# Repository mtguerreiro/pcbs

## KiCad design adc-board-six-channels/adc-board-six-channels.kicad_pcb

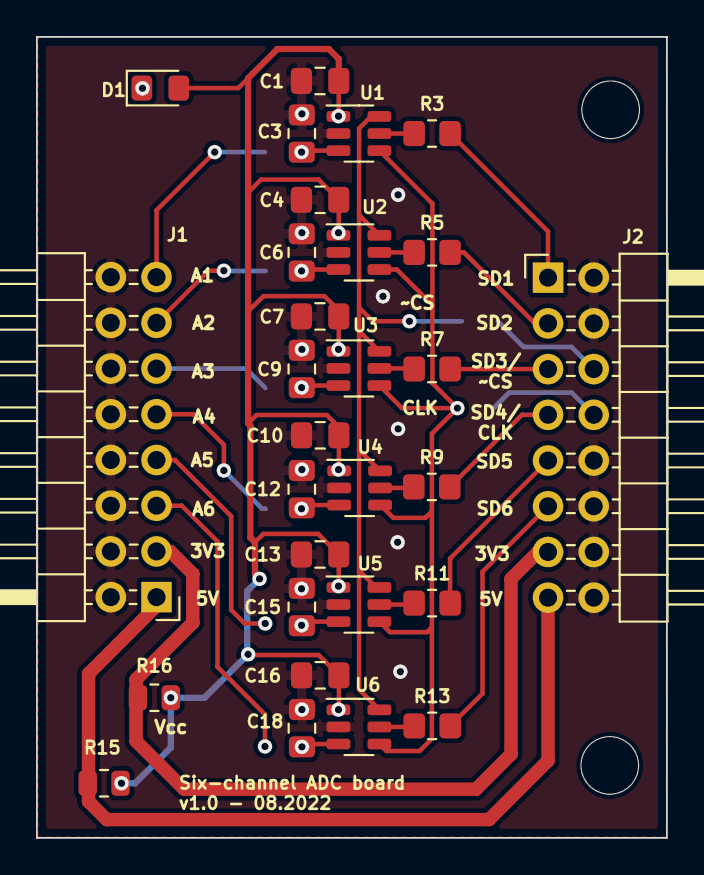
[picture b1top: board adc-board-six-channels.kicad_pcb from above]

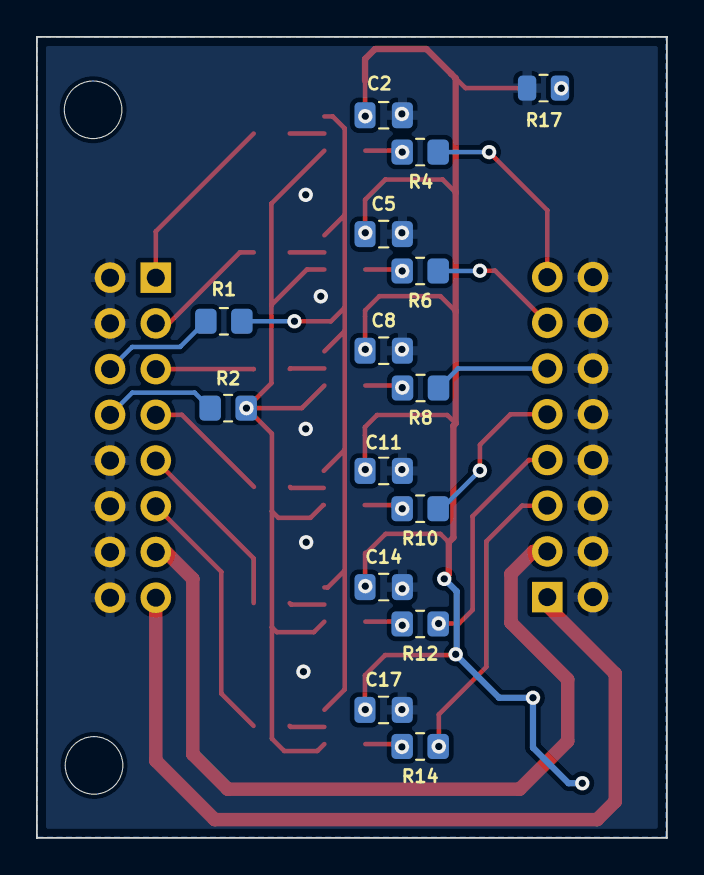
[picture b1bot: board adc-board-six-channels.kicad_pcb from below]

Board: 2 copper layers, 35.0 x 44.5 mm, 44 parts (15 on the bottom side), 33 nets.

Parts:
C1, C4, C7, C10, C13, C16: 1uF; C_0805_2012Metric_Pad1.18x1.45mm_HandSolder
C2, C5, C8, C11, C14, C17: 100nF; C_0805_2012Metric_Pad1.18x1.45mm_HandSolder
C3, C6, C9, C12, C15, C18: TBD; C_0805_2012Metric_Pad1.18x1.45mm_HandSolder
D1: LED; LED_0805_2012Metric_Pad1.15x1.40mm_HandSolder
J1, J2: Conn_02x08_Odd_Even; PinHeader_2x08_P2.54mm_Horizontal
R1, R2, R3, R5, R7, R9, R11, R13: 47R; R_0805_2012Metric_Pad1.20x1.40mm_HandSolder
R4, R6, R8, R10, R12, R14: TBD; R_0805_2012Metric_Pad1.20x1.40mm_HandSolder
R15: 0R; R_0805_2012Metric
R16: DNP; R_0805_2012Metric
R17: 2k; R_0805_2012Metric
U1, U2, U3, U4, U5, U6: ADC_SPI_GEN; TSOT-23-6

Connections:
+3V3: J1.3, J2.13, R16.2
+5V: J1.1, J2.15, R15.2
/A1: J1.15, R4.1
/A2: J1.13, R6.1
/A3: J1.11, R8.1
/A4: J1.9, R10.1
/A5: J1.7, R12.1
/A6: J1.5, R14.1
/SCLK: R2.2, U1.4 (SCLK), U2.4 (SCLK), U3.4 (SCLK), U4.4 (SCLK), U5.4 (SCLK), U6.4 (SCLK)
/SD1: J2.1, R3.2
/SD2: J2.3, R5.2
/SD3: J2.5, R7.2
/SD4: J2.7, R9.2
/SD5: J2.9, R11.2
/SD6: J2.11, R13.2
/~CS: R1.1, U1.6 (~CS), U2.6 (~CS), U3.6 (~CS), U4.6 (~CS), U5.6 (~CS), U6.6 (~CS)
GND: C1.2, C2.2, C3.2, C4.2, C5.2, C6.2, C7.2, C8.2, C9.2, C10.2, C11.2, C12.2, C13.2, C14.2, C15.2, C16.2, C17.2, C18.2, J1.2, J1.4, J1.6, J1.8, J1.10, J1.12, J1.14, J1.16, J2.2, J2.4, J2.10, J2.12, J2.14, J2.16, R17.2, U1.2 (GND), U2.2 (GND), U3.2 (GND), U4.2 (GND), U5.2 (GND), U6.2 (GND)
unnamed: C3.1, R4.2, U1.3 (AIN)
unnamed: C6.1, R6.2, U2.3 (AIN)
unnamed: C9.1, R8.2, U3.3 (AIN)
unnamed: C12.1, R10.2, U4.3 (AIN)
unnamed: C15.1, R12.2, U5.3 (AIN)
unnamed: C18.1, R14.2, U6.3 (AIN)
unnamed: D1.1 (K), R17.1
unnamed: J2.6, R1.2
unnamed: J2.8, R2.1
unnamed: R3.1, U1.5 (SDO)
unnamed: R5.1, U2.5 (SDO)
unnamed: R7.1, U3.5 (SDO)
unnamed: R9.1, U4.5 (SDO)
unnamed: R11.1, U5.5 (SDO)
unnamed: R13.1, U6.5 (SDO)
VCC: C1.1, C2.1, C4.1, C5.1, C7.1, C8.1, C10.1, C11.1, C13.1, C14.1, C16.1, C17.1, D1.2 (A), R15.1, R16.1, U1.1 (VDD), U2.1 (VDD), U3.1 (VDD), U4.1 (VDD), U5.1 (VDD), U6.1 (VDD)

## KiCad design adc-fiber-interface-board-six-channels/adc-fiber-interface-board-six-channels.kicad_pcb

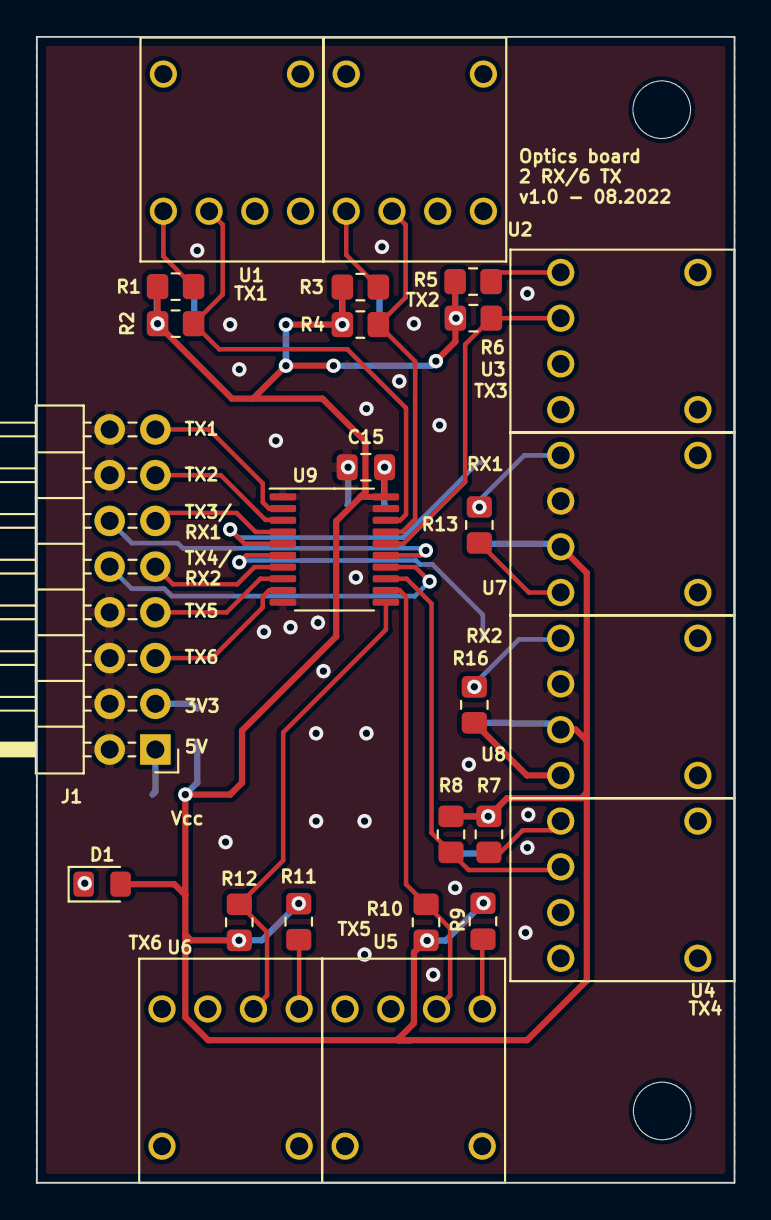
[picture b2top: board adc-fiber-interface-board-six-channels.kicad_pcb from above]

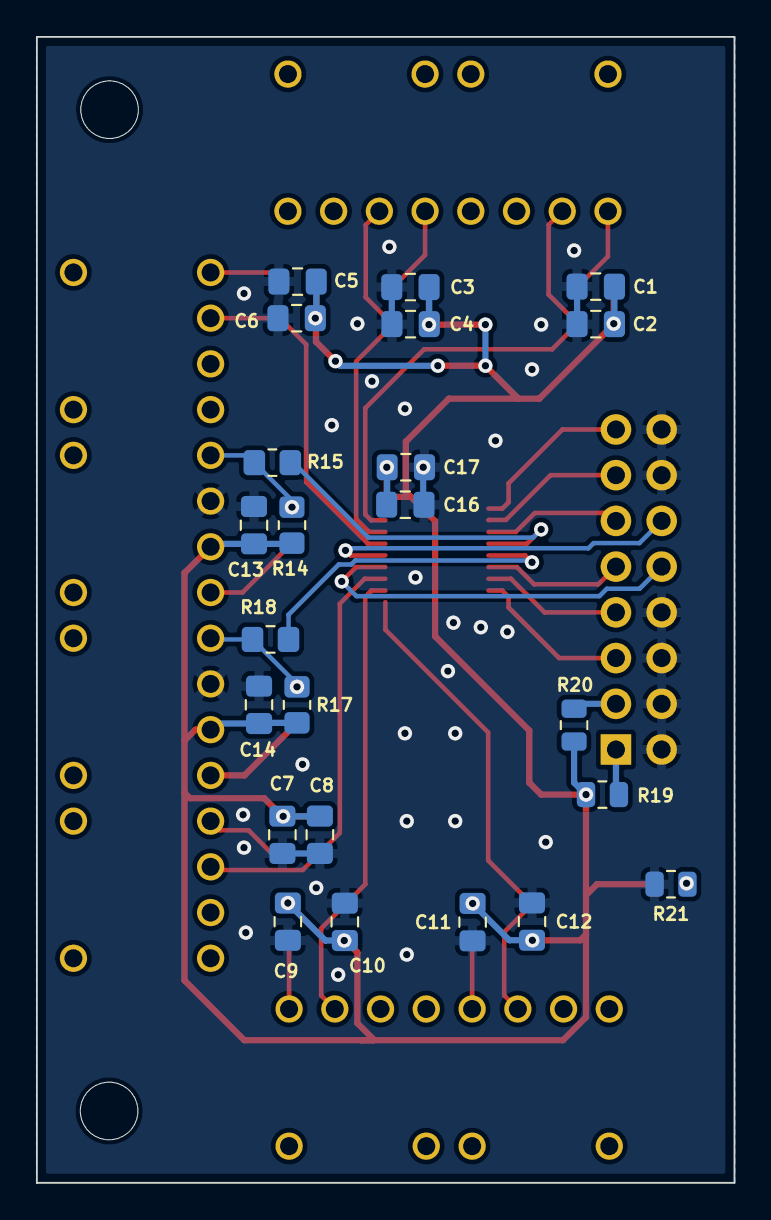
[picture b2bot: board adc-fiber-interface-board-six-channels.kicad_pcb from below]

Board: 2 copper layers, 38.8 x 63.7 mm, 49 parts (23 on the bottom side), 31 nets.

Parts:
C1, C3, C5, C7, C9, C11, C13, C14, C15, C16: 100nF; C_0805_2012Metric_Pad1.18x1.45mm_HandSolder
C2, C4, C6, C8, C10, C12, C17: 1uF; C_0805_2012Metric_Pad1.18x1.45mm_HandSolder
D1: LED; LED_0805_2012Metric_Pad1.15x1.40mm_HandSolder
J1: Conn_02x08_Odd_Even; PinHeader_2x08_P2.54mm_Horizontal
R1, R3, R5, R7, R9, R11: 220R; R_0805_2012Metric_Pad1.20x1.40mm_HandSolder
R2, R4, R6, R8, R10, R12: 2k; R_0805_2012Metric_Pad1.20x1.40mm_HandSolder
R13, R16: 0R; R_0805_2012Metric_Pad1.20x1.40mm_HandSolder
R14, R17: DNP; R_0805_2012Metric_Pad1.20x1.40mm_HandSolder
R15, R18: 47R; R_0805_2012Metric_Pad1.20x1.40mm_HandSolder
R19: 0R; R_0805_2012Metric
R20: DNP; R_0805_2012Metric
R21: 2k; R_0805_2012Metric
U1, U2, U3, U4, U5, U6: HFBR-1521Z
U7, U8: HFBR-2521Z
U9: 74HCT541; TSSOP-20_4.4x6.5mm_P0.65mm

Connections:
+3V3: J1.3, R20.2
+5V: J1.1, R19.2
/RX1: R15.1, U9.5 (A3)
/RX1b: J1.12, U9.15 (Y3)
/RX2: R18.1, U9.6 (A4)
/RX2b: J1.10, U9.14 (Y4)
/TX1: J1.15, U9.2 (A0)
/TX1b: R2.1, U1.2 (K), U9.18 (Y0)
/TX2: J1.13, U9.3 (A1)
/TX2b: R4.1, U2.2 (K), U9.17 (Y1)
/TX3: J1.11, U9.4 (A2)
/TX3b: R6.1, U3.2 (K), U9.16 (Y2)
/TX4: J1.9, U9.7 (A5)
/TX4b: R8.1, U4.2 (K), U9.13 (Y5)
/TX5: J1.7, U9.8 (A6)
/TX5b: R10.1, U5.2 (K), U9.12 (Y6)
/TX6: J1.5, U9.9 (A7)
/TX6b: R12.1, U6.2 (K), U9.11 (Y7)
GND: C1.1, C2.1, C3.1, C4.1, C5.1, C6.1, C7.1, C8.1, C9.1, C10.1, C11.1, C12.1, C13.1, C14.1, C15.1, C16.1, C17.1, J1.2, J1.4, J1.6, J1.8, J1.14, J1.16, R21.2, U7.2 (GND), U8.2 (GND), U9.1 (G1), U9.10 (GND), U9.19 (G2)
unnamed: D1.1 (K), R21.1
unnamed: R1.1, U1.1 (A)
unnamed: R3.1, U2.1 (A)
unnamed: R5.1, U3.1 (A)
unnamed: R7.1, U4.1 (A)
unnamed: R9.1, U5.1 (A)
unnamed: R11.1, U6.1 (A)
unnamed: R13.1, R14.1, R15.2, U7.1 (Vo)
unnamed: R13.2, U7.4 (RL)
unnamed: R16.1, R17.1, R18.2, U8.1 (Vo)
unnamed: R16.2, U8.4 (RL)
VCC: C1.2, C2.2, C3.2, C4.2, C5.2, C6.2, C7.2, C8.2, C9.2, C10.2, C11.2, C12.2, C13.2, C14.2, C15.2, C16.2, C17.2, D1.2 (A), R1.2, R2.2, R3.2, R4.2, R5.2, R6.2, R7.2, R8.2, R9.2, R10.2, R11.2, R12.2, R14.2, R17.2, R19.1, R20.1, U7.3 (Vcc), U8.3 (Vcc), U9.20 (VCC)

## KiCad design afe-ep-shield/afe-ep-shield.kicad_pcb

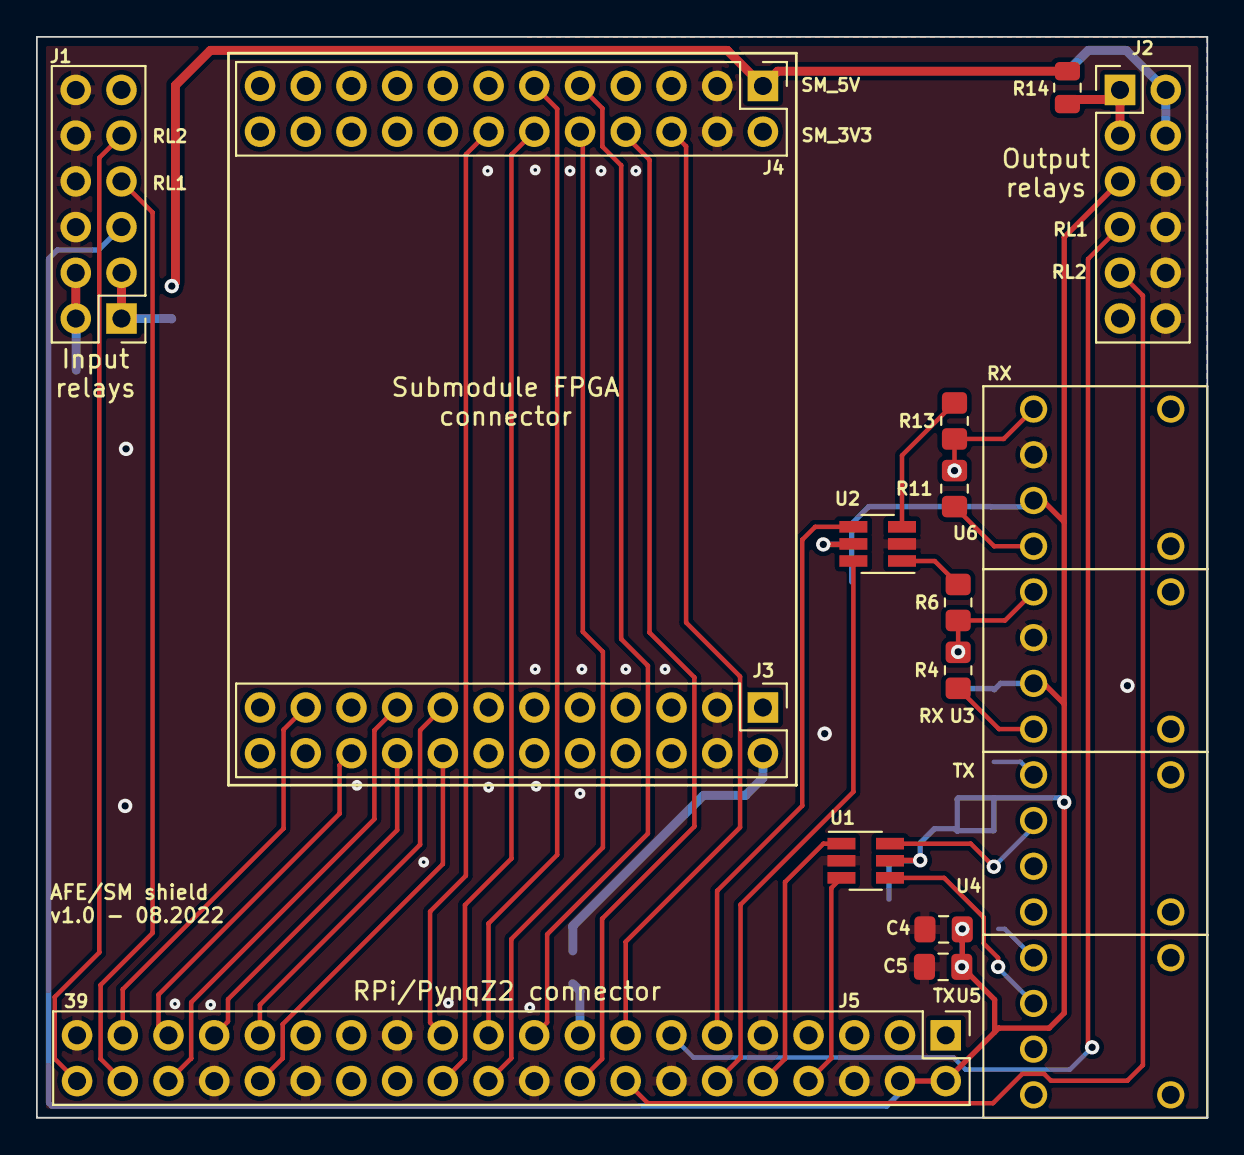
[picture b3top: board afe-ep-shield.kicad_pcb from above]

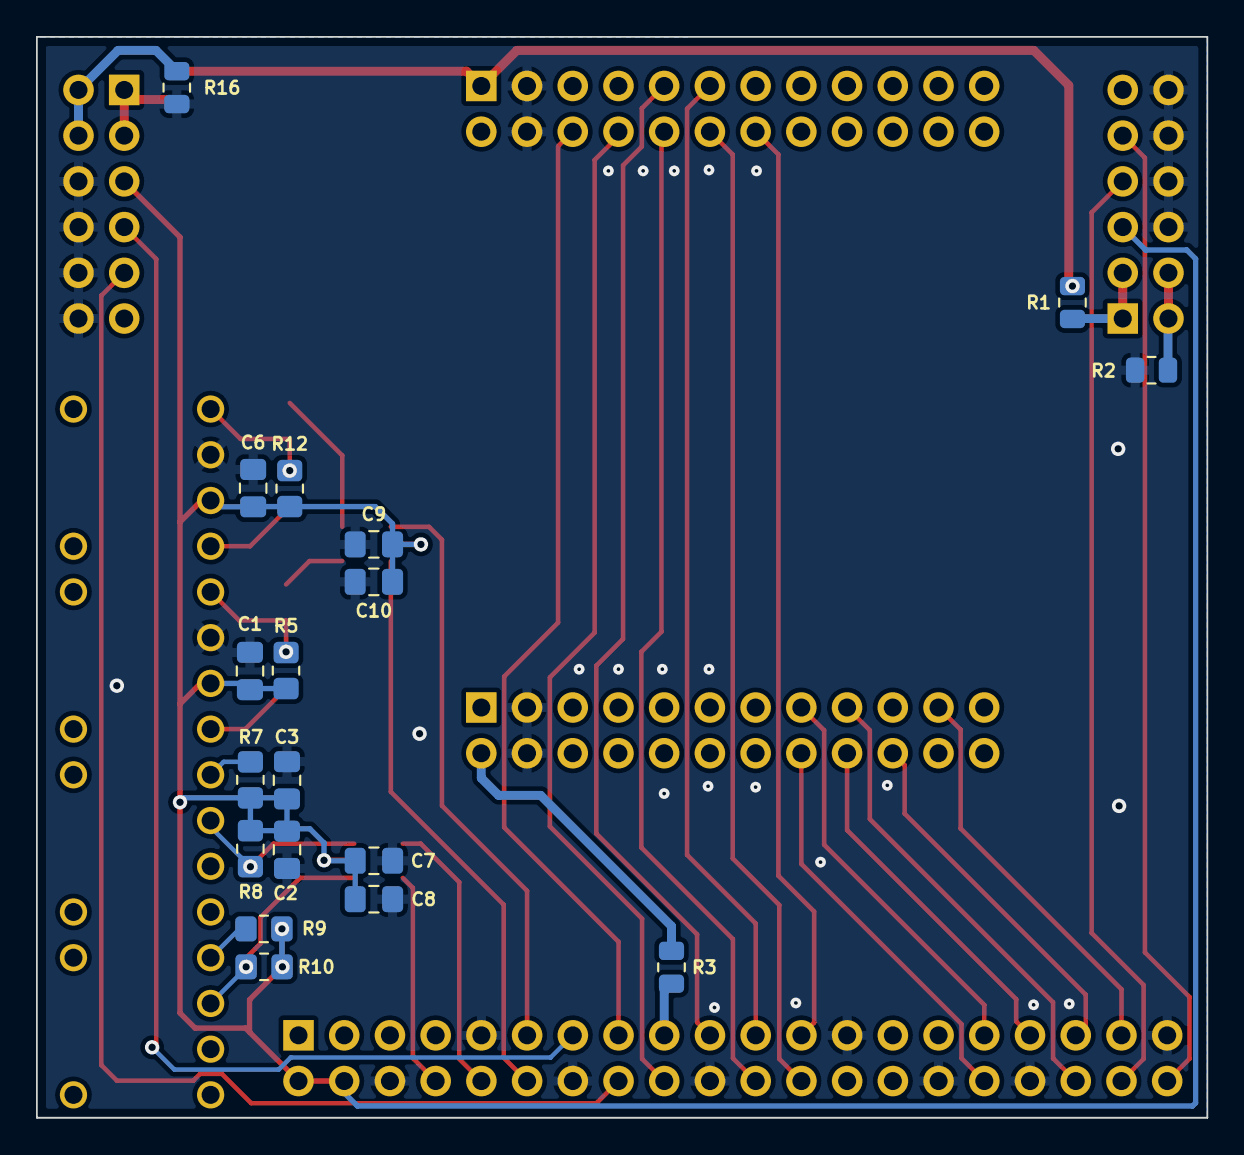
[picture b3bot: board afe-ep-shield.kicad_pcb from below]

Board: 2 copper layers, 65.0 x 60.0 mm, 36 parts (18 on the bottom side), 40 nets.

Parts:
C1, C2, C4, C6, C7, C9: 100nF; C_0805_2012Metric_Pad1.18x1.45mm_HandSolder
C3, C5, C8, C10: 1uF; C_0805_2012Metric_Pad1.18x1.45mm_HandSolder
J1, J2: Conn_02x06_Odd_Even; PinHeader_2x06_P2.54mm_Vertical
J3, J4: Conn_02x12_Odd_Even; PinHeader_2x12_P2.54mm_Vertical
J5: Conn_02x20_Odd_Even; PinHeader_2x20_P2.54mm_Vertical
R1, R2, R3, R14, R16: 0R; R_0805_2012Metric
R4, R11: 0R; R_0805_2012Metric_Pad1.20x1.40mm_HandSolder
R5, R12: DNP; R_0805_2012Metric_Pad1.20x1.40mm_HandSolder
R6, R13: 47R; R_0805_2012Metric_Pad1.20x1.40mm_HandSolder
R7, R9: 220R; R_0805_2012Metric_Pad1.20x1.40mm_HandSolder
R8, R10: 2k; R_0805_2012Metric_Pad1.20x1.40mm_HandSolder
U1, U2: Dual_Buffer; SOT-23-6_Handsoldering
U3, U6: HFBR-2521Z
U4, U5: HFBR-1521Z

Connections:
+3V3: J5.17, R3.1
+3V3A: J3.2, R3.2
+5V: C1.2, C2.2, C3.2, C4.2, C5.2, C6.2, C7.2, C8.2, C9.2, C10.2, J1.5, J2.5, J5.2, J5.4, R5.2, R7.2, R8.2, R9.2, R10.2, R12.2, U1.5 (Vcc), U2.5 (Vcc), U3.3 (Vcc), U6.3 (Vcc)
+5VA: J4.1, R1.2, R14.2
/EXT_CLK: J5.8, U1.3 (2A)
/EXT_CLK_f: R10.1, U1.4 (2Y), U5.2 (K)
/EXT_SD1: J5.12, U2.6 (1Y)
/EXT_SD1_f: R6.1, U2.1 (1A)
/EXT_SD2: J5.11, U2.4 (2Y)
/EXT_SD2_f: R13.1, U2.3 (2A)
/EXT_~CS: J5.10, U1.1 (1A)
/EXT_~CS_f: R8.1, U1.6 (1Y), U4.2 (K)
/I1_CLK: J3.17, J5.36
/I1_SD: J3.16, J5.32
/I1_~CS: J3.15, J5.31
/RL1_in: J1.7, J5.38
/RL1_out: J2.7, J5.13
/RL2_in: J1.9, J5.40
/RL2_out: J2.9, J5.16
/RPIO_08: J4.12, J5.24
/RPIO_09: J4.11, J5.21
/RPIO_10: J4.9, J5.19
/RPIO_11: J4.14, J5.23
/RPIO_13: J3.18, J5.33
/RPIO_19: J3.20, J5.35
/RPIO_22: J4.6, J5.15
/RPIO_24: J4.8, J5.18
/RPIO_25: J4.10, J5.22
/RPIO_26: J3.21, J5.37
GND: C1.1, C2.1, C3.1, C4.1, C5.1, C6.1, C7.1, C8.1, C9.1, C10.1, J1.6, J1.8, J1.10, J1.12, J2.6, J2.8, J2.10, J2.12, J3.3, J3.4, J4.3, J4.4, J5.6, J5.9, J5.14, J5.20, J5.25, J5.30, J5.34, J5.39, R2.1, R16.1, U1.2 (GND), U2.2 (GND), U3.2 (GND), U6.2 (GND)
GND1: J1.2, J1.4, R2.2
GND2: J2.2, J2.4, R16.2
unnamed: R4.1, R5.1, R6.2, U3.1 (Vo)
unnamed: R4.2, U3.4 (RL)
unnamed: R7.1, U4.1 (A)
unnamed: R9.1, U5.1 (A)
unnamed: R11.1, R12.1, R13.2, U6.1 (Vo)
unnamed: R11.2, U6.4 (RL)
VCC: J2.1, J2.3, R14.1
VDC: J1.1, J1.3, R1.1

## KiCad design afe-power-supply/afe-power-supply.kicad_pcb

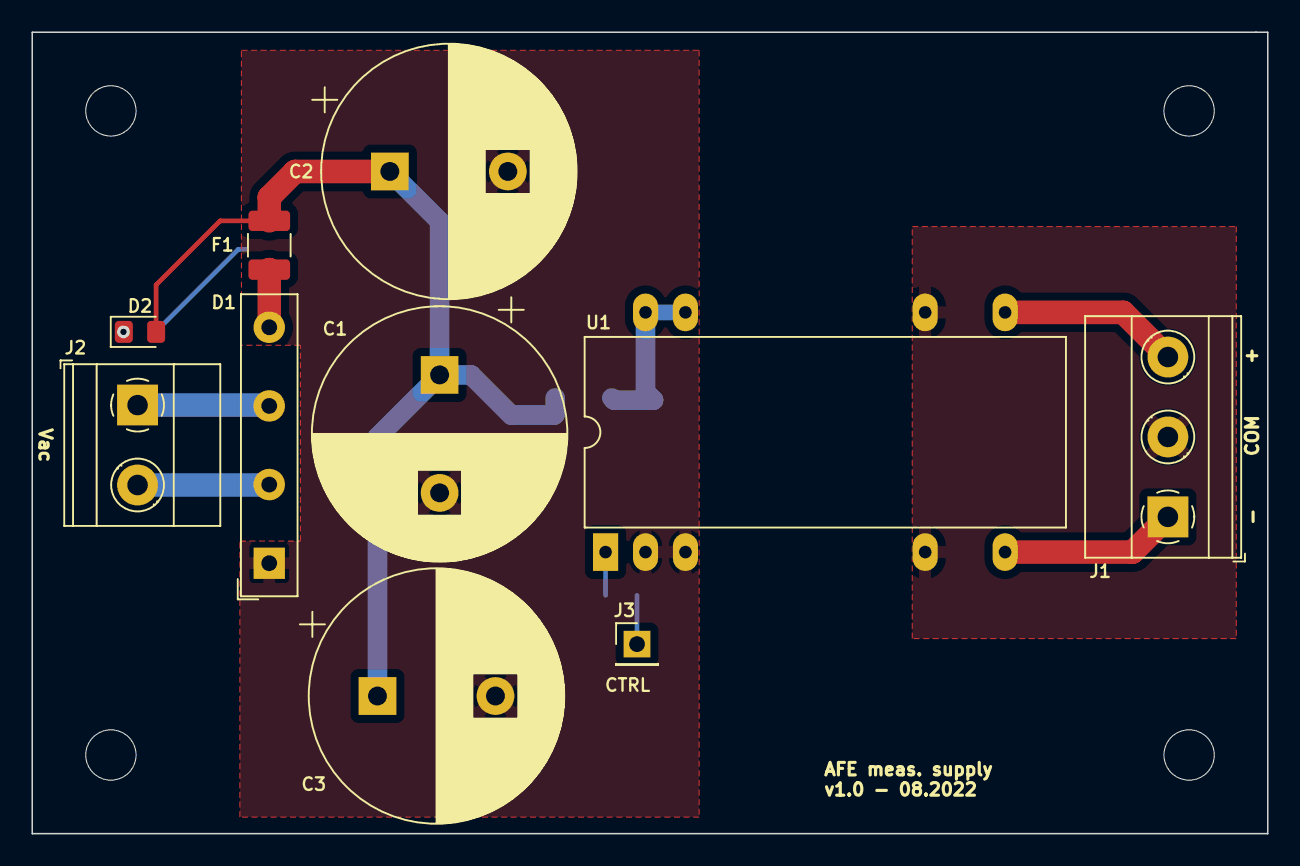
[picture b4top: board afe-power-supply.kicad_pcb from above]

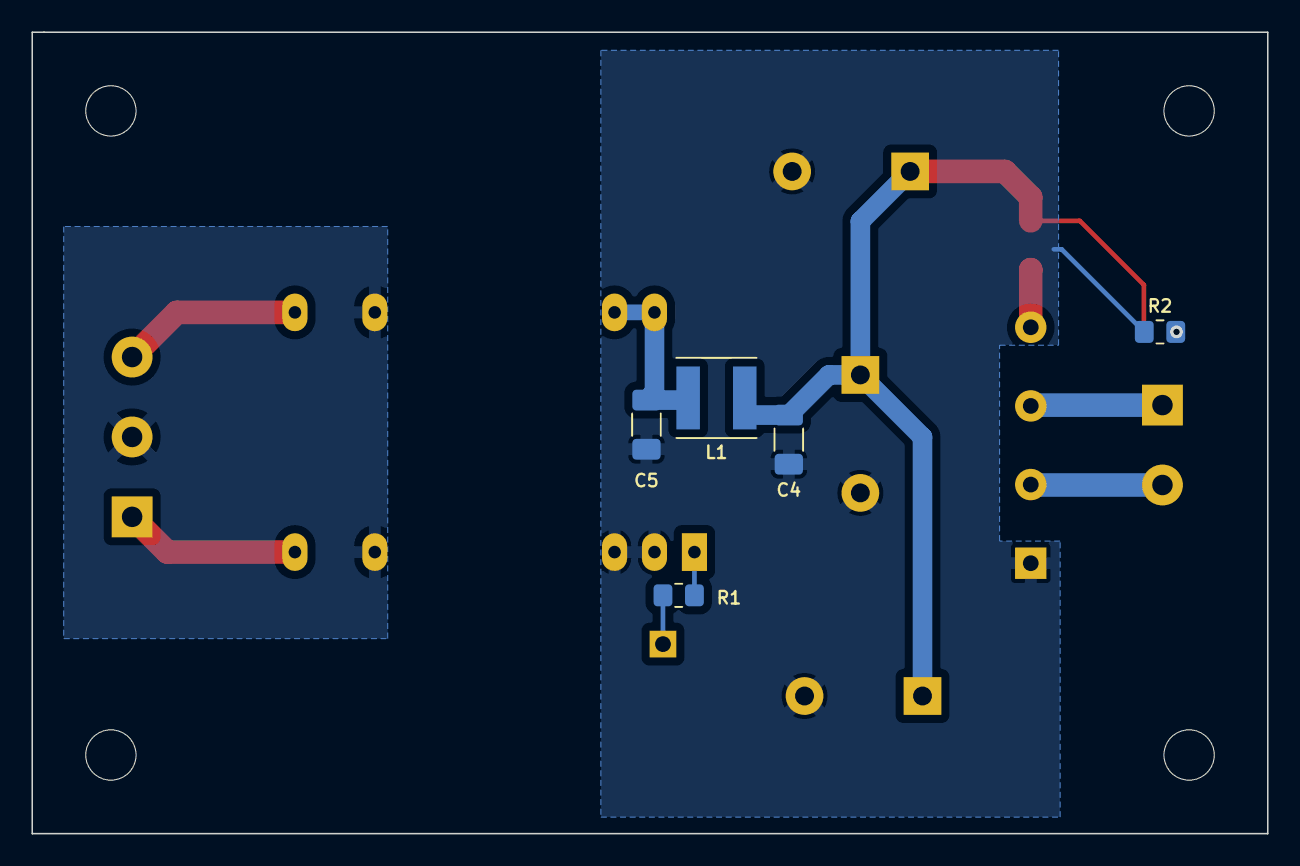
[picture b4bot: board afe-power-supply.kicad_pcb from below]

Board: 2 copper layers, 78.5 x 50.9 mm, 15 parts (5 on the bottom side), 12 nets.

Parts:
C1, C2, C3: TBD; CP_Radial_D16.0mm_P7.50mm
C4, C5: 10uF; C_1206_3216Metric_Pad1.33x1.80mm_HandSolder
D1: D_Bridge_-AA+; Diode_Bridge_19.0x3.5x10.0mm_P5.0mm
D2: LED; LED_0805_2012Metric_Pad1.15x1.40mm_HandSolder
F1: Polyfuse; R_1210_3225Metric_Pad1.30x2.65mm_HandSolder
J1: Screw_Terminal_01x03; TerminalBlock_Phoenix_MKDS-1,5-3-5.08_1x03_P5.08mm_Horizont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
J2: Screw_Terminal_01x02; TerminalBlock_Phoenix_MKDS-1,5-2-5.08_1x02_P5.08mm_Horizont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
J3: Conn_01x01; PinHeader_1x01_P2.54mm_Vertical
L1: 50uH; L_Taiyo-Yuden_NR-50xx
R1: DNP; R_0805_2012Metric_Pad1.20x1.40mm_HandSolder
R2: 2k; R_0805_2012Metric_Pad1.20x1.40mm_HandSolder
U1: Generic_DIP24_Dual_Isolated_DCDC

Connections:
/GND: J1.2, U1.9 (COM), U1.16 (COM)
/V_AC_+: D1.2, J2.2
/V_AC_-: D1.3, J2.1
/V_DC_+: C1.1, C2.1, C3.1, C4.1, D2.2 (A), F1.2, L1.1
/V_DC_-: C1.2, C2.2, C3.2, C4.2, C5.2, D1.1 (-), R2.2, U1.2 (Vin-), U1.3 (Vin-)
/V_DC_FILT_+: C5.1, L1.2, U1.22 (Vin+), U1.23 (Vin+)
/Vout+: J1.3, U1.14 (Vout+)
/Vout-: J1.1, U1.11 (Vout-)
unnamed: D1.4 (+), F1.1
unnamed: D2.1 (K), R2.1
unnamed: J3.1, R1.2
unnamed: R1.1, U1.1 (CTRL)

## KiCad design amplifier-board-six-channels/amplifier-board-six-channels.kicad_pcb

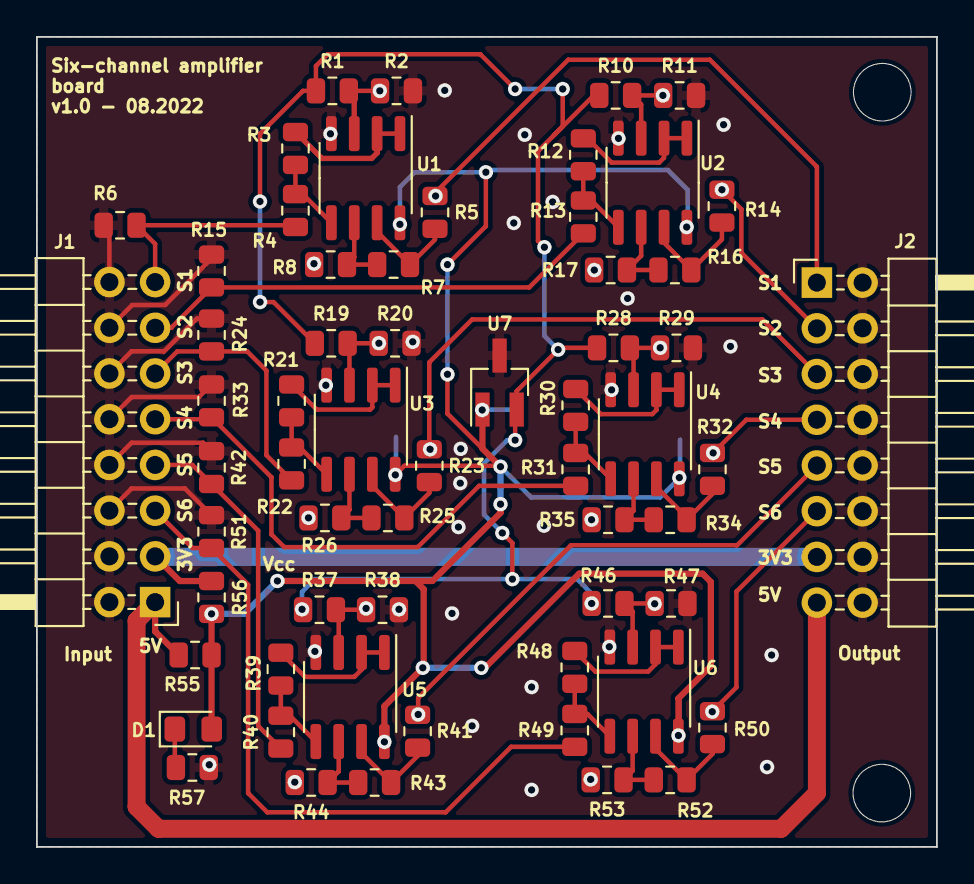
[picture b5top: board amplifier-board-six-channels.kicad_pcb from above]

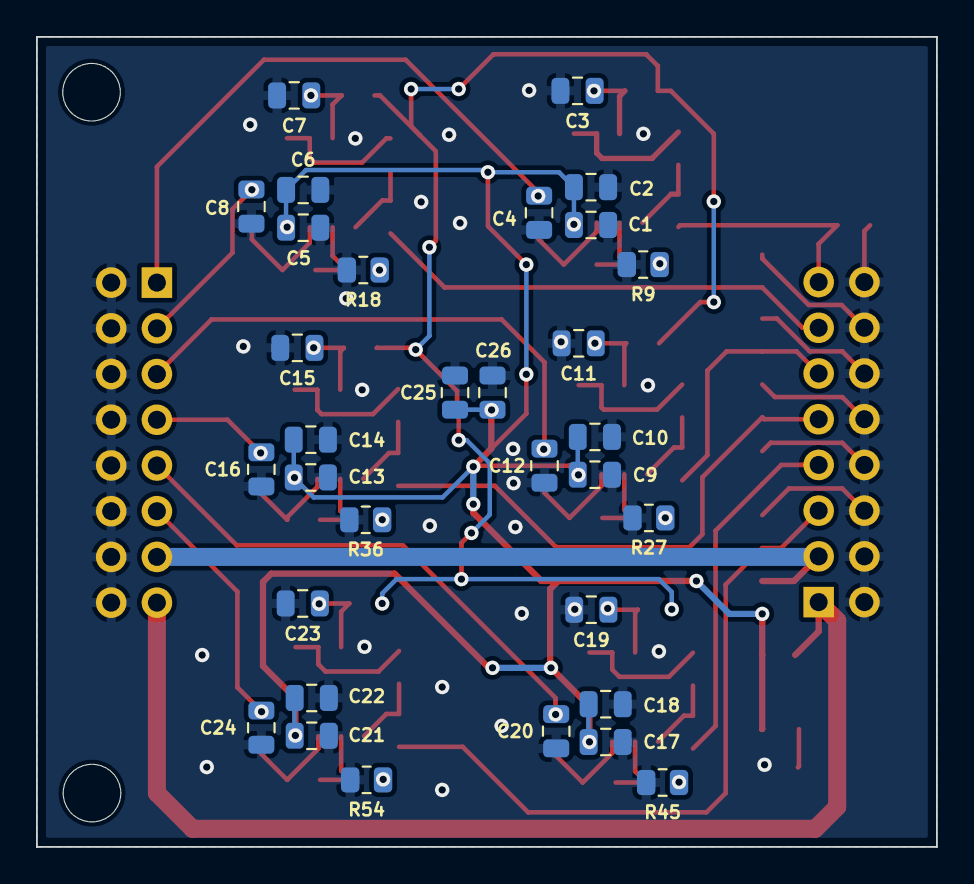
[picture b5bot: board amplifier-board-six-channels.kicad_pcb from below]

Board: 2 copper layers, 50.0 x 45.0 mm, 93 parts (32 on the bottom side), 54 nets.

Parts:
C1, C3, C5, C7, C9, C11, C13, C15, C17, C19, C21, C23, C26: 100nF; C_0805_2012Metric
C2, C6, C10, C14, C18, C22, C25: 1uF; C_0805_2012Metric
C4, C8, C12, C16, C20, C24: TBD; C_0805_2012Metric
D1: LED; LED_0805_2012Metric_Pad1.15x1.40mm_HandSolder
J1, J2: Conn_02x08_Odd_Even; PinHeader_2x08_P2.54mm_Horizontal
R1, R2, R3, R4, R6, R7, R8, R9, R10, R11, R12, R13, R15, R16, R17, R18, R19, R20, R21, R22, R24, R25, R26, R27, R28, R29, R30, R31, R33, R34, R35, R36, R37, R38, R39, R40, R42, R43, R44, R45, R46, R47, R48, R49, R51, R52, R53, R54, R57: TBD; R_0805_2012Metric
R5, R14, R23, R32, R41, R50, R55: 0R; R_0805_2012Metric
R56: DNP; R_0805_2012Metric
U1, U2, U3, U4, U5, U6: Opamp_Dual; SOIC-8_3.9x4.9mm_P1.27mm
U7: MAX6035xxUR25; SOT-23_Handsoldering

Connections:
+3V3: J1.3, J2.13, R56.2
+5V: J1.1, J2.15, R55.2
/S1i: J1.15, R4.1, R6.1
/S1o: C4.1, J2.1, R5.2
/S2i: J1.13, R13.1, R15.1
/S2o: C8.1, J2.3, R14.2
/S3i: J1.11, R22.1, R24.1
/S3o: C12.1, J2.5, R23.2
/S4i: J1.9, R31.1, R33.1
/S4o: C16.1, J2.7, R32.2
/S5i: J1.7, R40.1, R42.1
/S5o: C20.1, J2.9, R41.2
/S6i: J1.5, R49.1, R51.1
/S6o: C24.1, J2.11, R50.2
/V_ref: R1.1, R10.1, R19.1, R28.1, R37.1, R46.1, U7.2 (OUT)
/sigcond1/V_ref': R3.1, U1.1, U1.2 (-)
/sigcond2/V_ref': R12.1, U2.1, U2.2 (-)
/sigcond3/V_ref': R21.1, U3.1, U3.2 (-)
/sigcond4/V_ref': R30.1, U4.1, U4.2 (-)
/sigcond5/V_ref': R39.1, U5.1, U5.2 (-)
/sigcond6/V_ref': R48.1, U6.1, U6.2 (-)
GND: C1.2, C2.2, C3.2, C4.2, C5.2, C6.2, C7.2, C8.2, C9.2, C10.2, C11.2, C12.2, C13.2, C14.2, C15.2, C16.2, C17.2, C18.2, C19.2, C20.2, C21.2, C22.2, C23.2, C24.2, C25.2, C26.2, J1.2, J1.4, J1.6, J1.8, J1.10, J1.12, J1.14, J1.16, J2.2, J2.4, J2.6, J2.8, J2.10, J2.12, J2.14, J2.16, R2.2, R6.2, R9.2, R11.2, R15.2, R18.2, R20.2, R24.2, R27.2, R29.2, R33.2, R36.2, R38.2, R42.2, R45.2, R47.2, R51.2, R54.2, R57.2, U1.4 (V-), U2.4 (V-), U3.4 (V-), U4.4 (V-), U5.4 (V-), U6.4 (V-), U7.3 (GND)
unnamed: C3.1, R1.2, R2.1, U1.3 (+)
unnamed: C7.1, R10.2, R11.1, U2.3 (+)
unnamed: C11.1, R19.2, R20.1, U3.3 (+)
unnamed: C15.1, R28.2, R29.1, U4.3 (+)
unnamed: C19.1, R37.2, R38.1, U5.3 (+)
unnamed: C23.1, R46.2, R47.1, U6.3 (+)
unnamed: D1.1 (K), R57.1
unnamed: R3.2, R4.2, U1.5 (+)
unnamed: R5.1, R7.2, U1.7
unnamed: R7.1, R8.1, U1.6 (-)
unnamed: R8.2, R9.1
unnamed: R12.2, R13.2, U2.5 (+)
unnamed: R14.1, R16.2, U2.7
unnamed: R16.1, R17.1, U2.6 (-)
unnamed: R17.2, R18.1
unnamed: R21.2, R22.2, U3.5 (+)
unnamed: R23.1, R25.2, U3.7
unnamed: R25.1, R26.1, U3.6 (-)
unnamed: R26.2, R27.1
unnamed: R30.2, R31.2, U4.5 (+)
unnamed: R32.1, R34.2, U4.7
unnamed: R34.1, R35.1, U4.6 (-)
unnamed: R35.2, R36.1
unnamed: R39.2, R40.2, U5.5 (+)
unnamed: R41.1, R43.2, U5.7
unnamed: R43.1, R44.1, U5.6 (-)
unnamed: R44.2, R45.1
unnamed: R48.2, R49.2, U6.5 (+)
unnamed: R50.1, R52.2, U6.7
unnamed: R52.1, R53.1, U6.6 (-)
unnamed: R53.2, R54.1
VCC: C1.1, C2.1, C5.1, C6.1, C9.1, C10.1, C13.1, C14.1, C17.1, C18.1, C21.1, C22.1, C25.1, C26.1, D1.2 (A), R55.1, R56.1, U1.8 (V+), U2.8 (V+), U3.8 (V+), U4.8 (V+), U5.8 (V+), U6.8 (V+), U7.1 (IN)

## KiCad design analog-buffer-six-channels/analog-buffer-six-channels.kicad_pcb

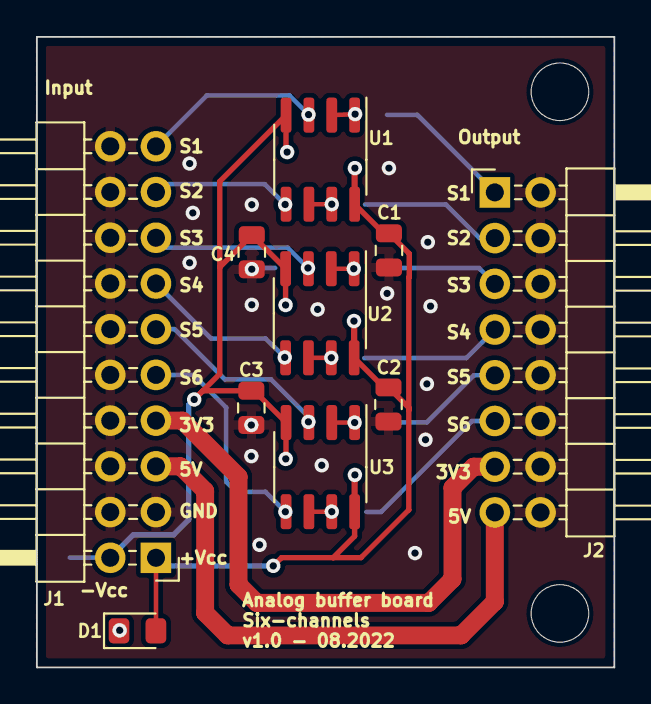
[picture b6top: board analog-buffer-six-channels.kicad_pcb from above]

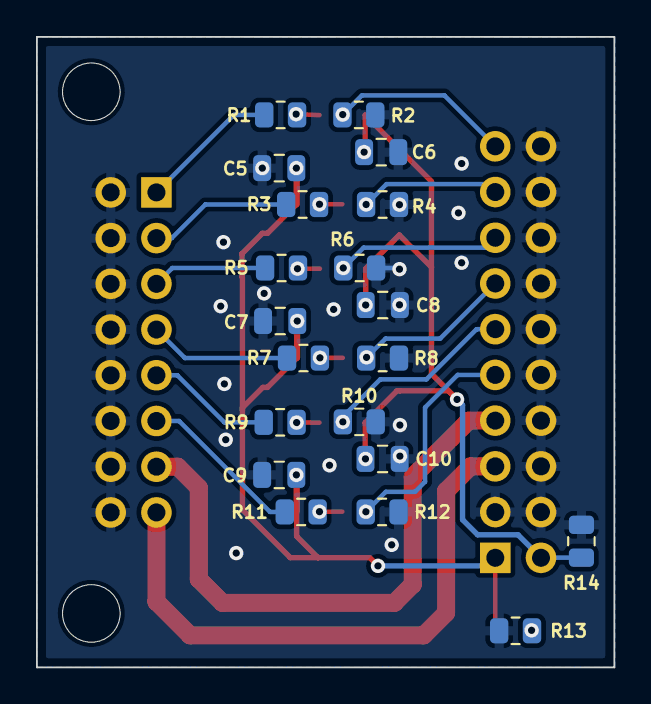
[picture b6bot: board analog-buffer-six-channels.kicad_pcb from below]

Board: 2 copper layers, 32.1 x 35.0 mm, 30 parts (20 on the bottom side), 24 nets.

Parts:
C1, C2, C3, C4: 10uF; C_0805_2012Metric
C5, C6, C7, C8, C9, C10: 100nF; C_0805_2012Metric
D1: LED; LED_0805_2012Metric_Pad1.15x1.40mm_HandSolder
J1: Conn_02x10_Odd_Even; PinHeader_2x10_P2.54mm_Horizontal
J2: Conn_02x08_Odd_Even; PinHeader_2x08_P2.54mm_Horizontal
R1, R3, R5, R7, R9, R11: 0R; R_0805_2012Metric
R2, R4, R6, R8, R10, R12, R13: TBD; R_0805_2012Metric
R14: DNP; R_0805_2012Metric
U1, U2, U3: Opamp_Dual; SOIC-8_3.9x4.9mm_P1.27mm

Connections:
+3V3: J1.7, J2.13
+5V: J1.5, J2.15
+VCC: C1.1, C2.1, C5.1, C7.1, C9.1, D1.2 (A), J1.1, U1.8 (V+), U2.8 (V+), U3.8 (V+)
-VCC: C3.2, C4.2, C6.1, C8.1, C10.1, J1.2, R14.1, U1.4 (V-), U2.4 (V-), U3.4 (V-)
/S1i: J1.19, R2.2, U1.3 (+)
/S1o: J2.1, R1.2
/S2i: J1.17, R4.2, U1.5 (+)
/S2o: J2.3, R3.2
/S3i: J1.15, R6.2, U2.3 (+)
/S3o: J2.5, R5.2
/S4i: J1.13, R8.2, U2.5 (+)
/S4o: J2.7, R7.2
/S5i: J1.11, R10.2, U3.3 (+)
/S5o: J2.9, R9.2
/S6i: J1.9, R12.2, U3.5 (+)
/S6o: J2.11, R11.2
GND: C1.2, C2.2, C3.1, C4.1, C5.2, C6.2, C7.2, C8.2, C9.2, C10.2, J1.3, J1.4, J1.6, J1.8, J1.10, J1.12, J1.14, J1.16, J1.18, J1.20, J2.2, J2.4, J2.6, J2.8, J2.10, J2.12, J2.14, J2.16, R2.1, R4.1, R6.1, R8.1, R10.1, R12.1, R13.2, R14.2
unnamed: D1.1 (K), R13.1
unnamed: R1.1, U1.1, U1.2 (-)
unnamed: R3.1, U1.6 (-), U1.7
unnamed: R5.1, U2.1, U2.2 (-)
unnamed: R7.1, U2.6 (-), U2.7
unnamed: R9.1, U3.1, U3.2 (-)
unnamed: R11.1, U3.6 (-), U3.7

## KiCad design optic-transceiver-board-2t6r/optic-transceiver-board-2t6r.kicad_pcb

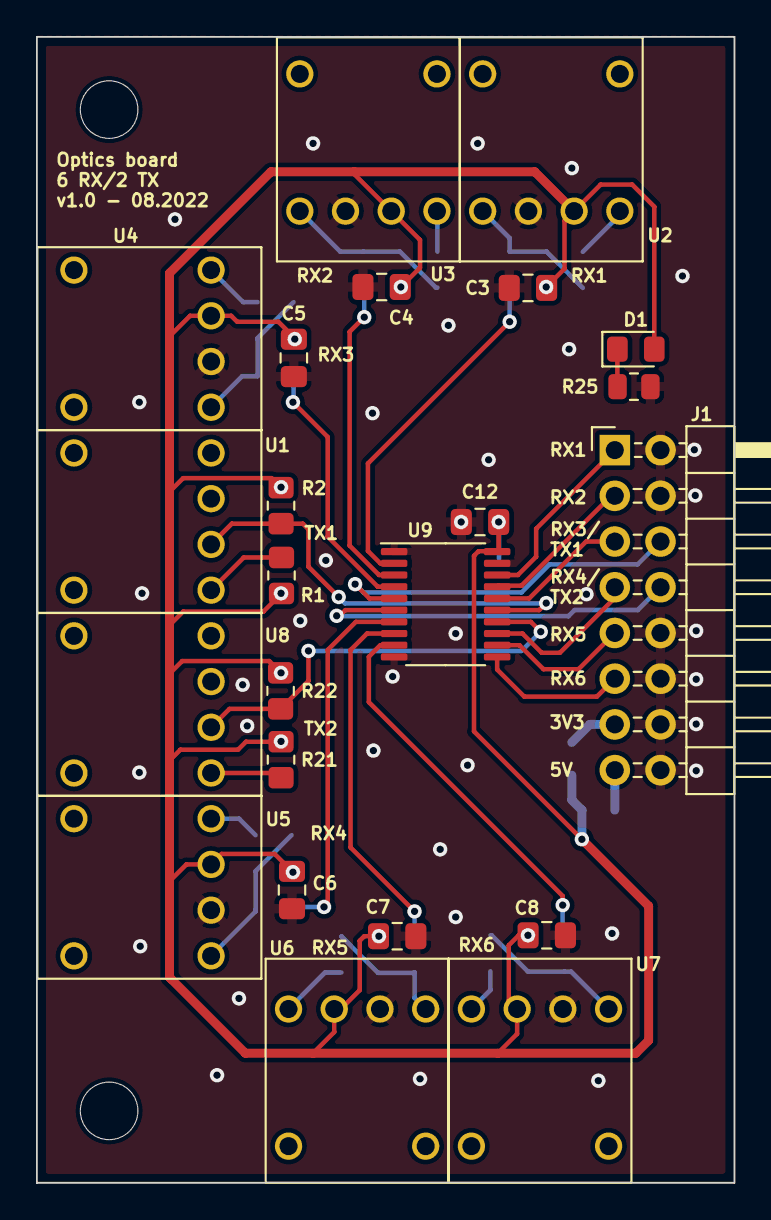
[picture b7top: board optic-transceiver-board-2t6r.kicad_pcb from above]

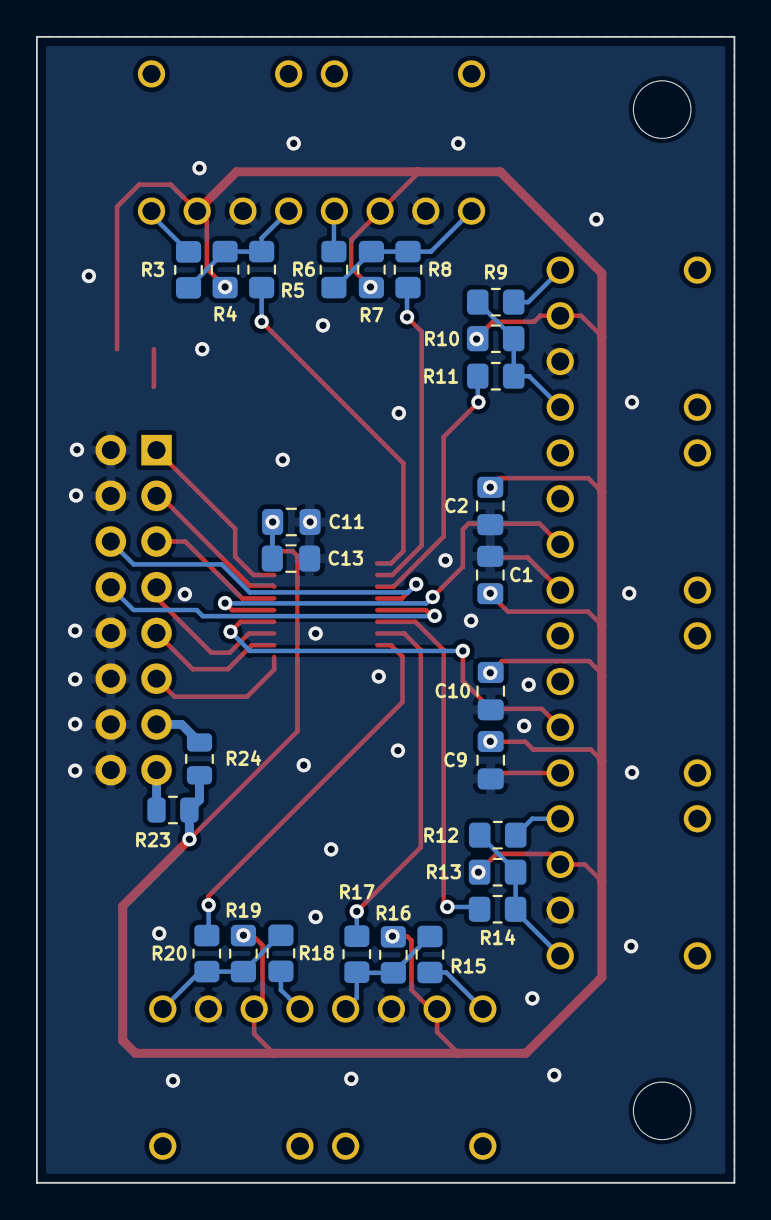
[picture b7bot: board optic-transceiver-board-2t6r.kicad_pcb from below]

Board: 2 copper layers, 38.8 x 63.7 mm, 49 parts (26 on the bottom side), 35 nets.

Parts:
C1, C3, C4, C5, C6, C7, C8, C9, C11, C12: 100nF; C_0805_2012Metric_Pad1.18x1.45mm_HandSolder
C2, C10, C13: 1uF; C_0805_2012Metric_Pad1.18x1.45mm_HandSolder
D1: LED; LED_0805_2012Metric_Pad1.15x1.40mm_HandSolder
J1: Conn_02x08_Odd_Even; PinHeader_2x08_P2.54mm_Horizontal
R1, R21: 220R; R_0805_2012Metric_Pad1.20x1.40mm_HandSolder
R2, R22: 2k; R_0805_2012Metric_Pad1.20x1.40mm_HandSolder
R3, R6, R9, R12, R15, R18: 0R; R_0805_2012Metric_Pad1.20x1.40mm_HandSolder
R4, R7, R10, R13, R16, R19: DNP; R_0805_2012Metric_Pad1.20x1.40mm_HandSolder
R5, R8, R11, R14, R17, R20: 47R; R_0805_2012Metric_Pad1.20x1.40mm_HandSolder
R23: 0R; R_0805_2012Metric
R24: DNP; R_0805_2012Metric
R25: 2k; R_0805_2012Metric
U1, U8: HFBR-1521Z
U2, U3, U4, U5, U6, U7: HFBR-2521Z
U9: 74HCT541; TSSOP-20_4.4x6.5mm_P0.65mm

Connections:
+3V3: J1.13, R24.2
+5V: J1.15, R23.2
/RX1: R5.1, U9.2 (A0)
/RX1b: J1.1, U9.18 (Y0)
/RX2: R8.1, U9.3 (A1)
/RX2b: J1.3, U9.17 (Y1)
/RX3: R11.1, U9.4 (A2)
/RX3b: J1.5, U9.16 (Y2)
/RX4: R14.1, U9.7 (A5)
/RX4b: J1.7, U9.13 (Y5)
/RX5: R17.1, U9.8 (A6)
/RX5b: J1.9, U9.12 (Y6)
/RX6: R20.1, U9.9 (A7)
/RX6b: J1.11, U9.11 (Y7)
/TX1: J1.6, U9.5 (A3)
/TX1b: R2.1, U1.2 (K), U9.15 (Y3)
/TX2: J1.8, U9.6 (A4)
/TX2b: R22.1, U8.2 (K), U9.14 (Y4)
GND: C1.1, C2.1, C3.1, C4.1, C5.1, C6.1, C7.1, C8.1, C9.1, C10.1, C11.1, C12.1, C13.1, J1.2, J1.4, J1.10, J1.12, J1.14, J1.16, R25.2, U2.2 (GND), U3.2 (GND), U4.2 (GND), U5.2 (GND), U6.2 (GND), U7.2 (GND), U9.1 (G1), U9.10 (GND), U9.19 (G2)
unnamed: D1.1 (K), R25.1
unnamed: R1.1, U1.1 (A)
unnamed: R3.1, R4.1, R5.2, U2.1 (Vo)
unnamed: R3.2, U2.4 (RL)
unnamed: R6.1, R7.1, R8.2, U3.1 (Vo)
unnamed: R6.2, U3.4 (RL)
unnamed: R9.2, U4.4 (RL)
unnamed: R9.1, R10.1, R11.2, U4.1 (Vo)
unnamed: R12.1, R13.1, R14.2, U5.1 (Vo)
unnamed: R12.2, U5.4 (RL)
unnamed: R15.1, R16.1, R17.2, U6.1 (Vo)
unnamed: R15.2, U6.4 (RL)
unnamed: R18.1, R19.1, R20.2, U7.1 (Vo)
unnamed: R18.2, U7.4 (RL)
unnamed: R21.1, U8.1 (A)
VCC: C1.2, C2.2, C3.2, C4.2, C5.2, C6.2, C7.2, C8.2, C9.2, C10.2, C11.2, C12.2, C13.2, D1.2 (A), R1.2, R2.2, R4.2, R7.2, R10.2, R13.2, R16.2, R19.2, R21.2, R22.2, R23.1, R24.1, U2.3 (Vcc), U3.3 (Vcc), U4.3 (Vcc), U5.3 (Vcc), U6.3 (Vcc), U7.3 (Vcc), U9.20 (VCC)
